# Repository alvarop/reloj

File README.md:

# Reloj - 7400 Series Digital Clock

This project was inspired by my dad's university digital systems project from the late 1970's. I found the writeup and schematic and decided to try and re-create it. You can see the results of the breadboard reproduction and explanations in [this twitter thread.](https://twitter.com/alvaroprieto/status/1239990814320680960)

After a while, I figured it would be fun to make a soldering kit out of it, which resulted in this.

The design is fairly close to the original, but with the addition of a crystal-backed alternate clock source. The 555 timer clock source works, but drifts like crazy, so if you want to use it as an actual clock, you still can with the alt source.

If you want to take a look at the actual paper, you can see the scanned version [here](files/sistemas_digitales.pdf).

## Design Files
You can get the latest files in the [github releases](https://github.com/alvarop/reloj/releases).

For v1.2, you can use my [OSHPark shared project](https://oshpark.com/shared_projects/LdUSEX5V) or by grabbing the gerbers from the release.

## Assembly Instructions
You can find semi-detailed assembly instructions [here](INSTRUCTIONS.md).

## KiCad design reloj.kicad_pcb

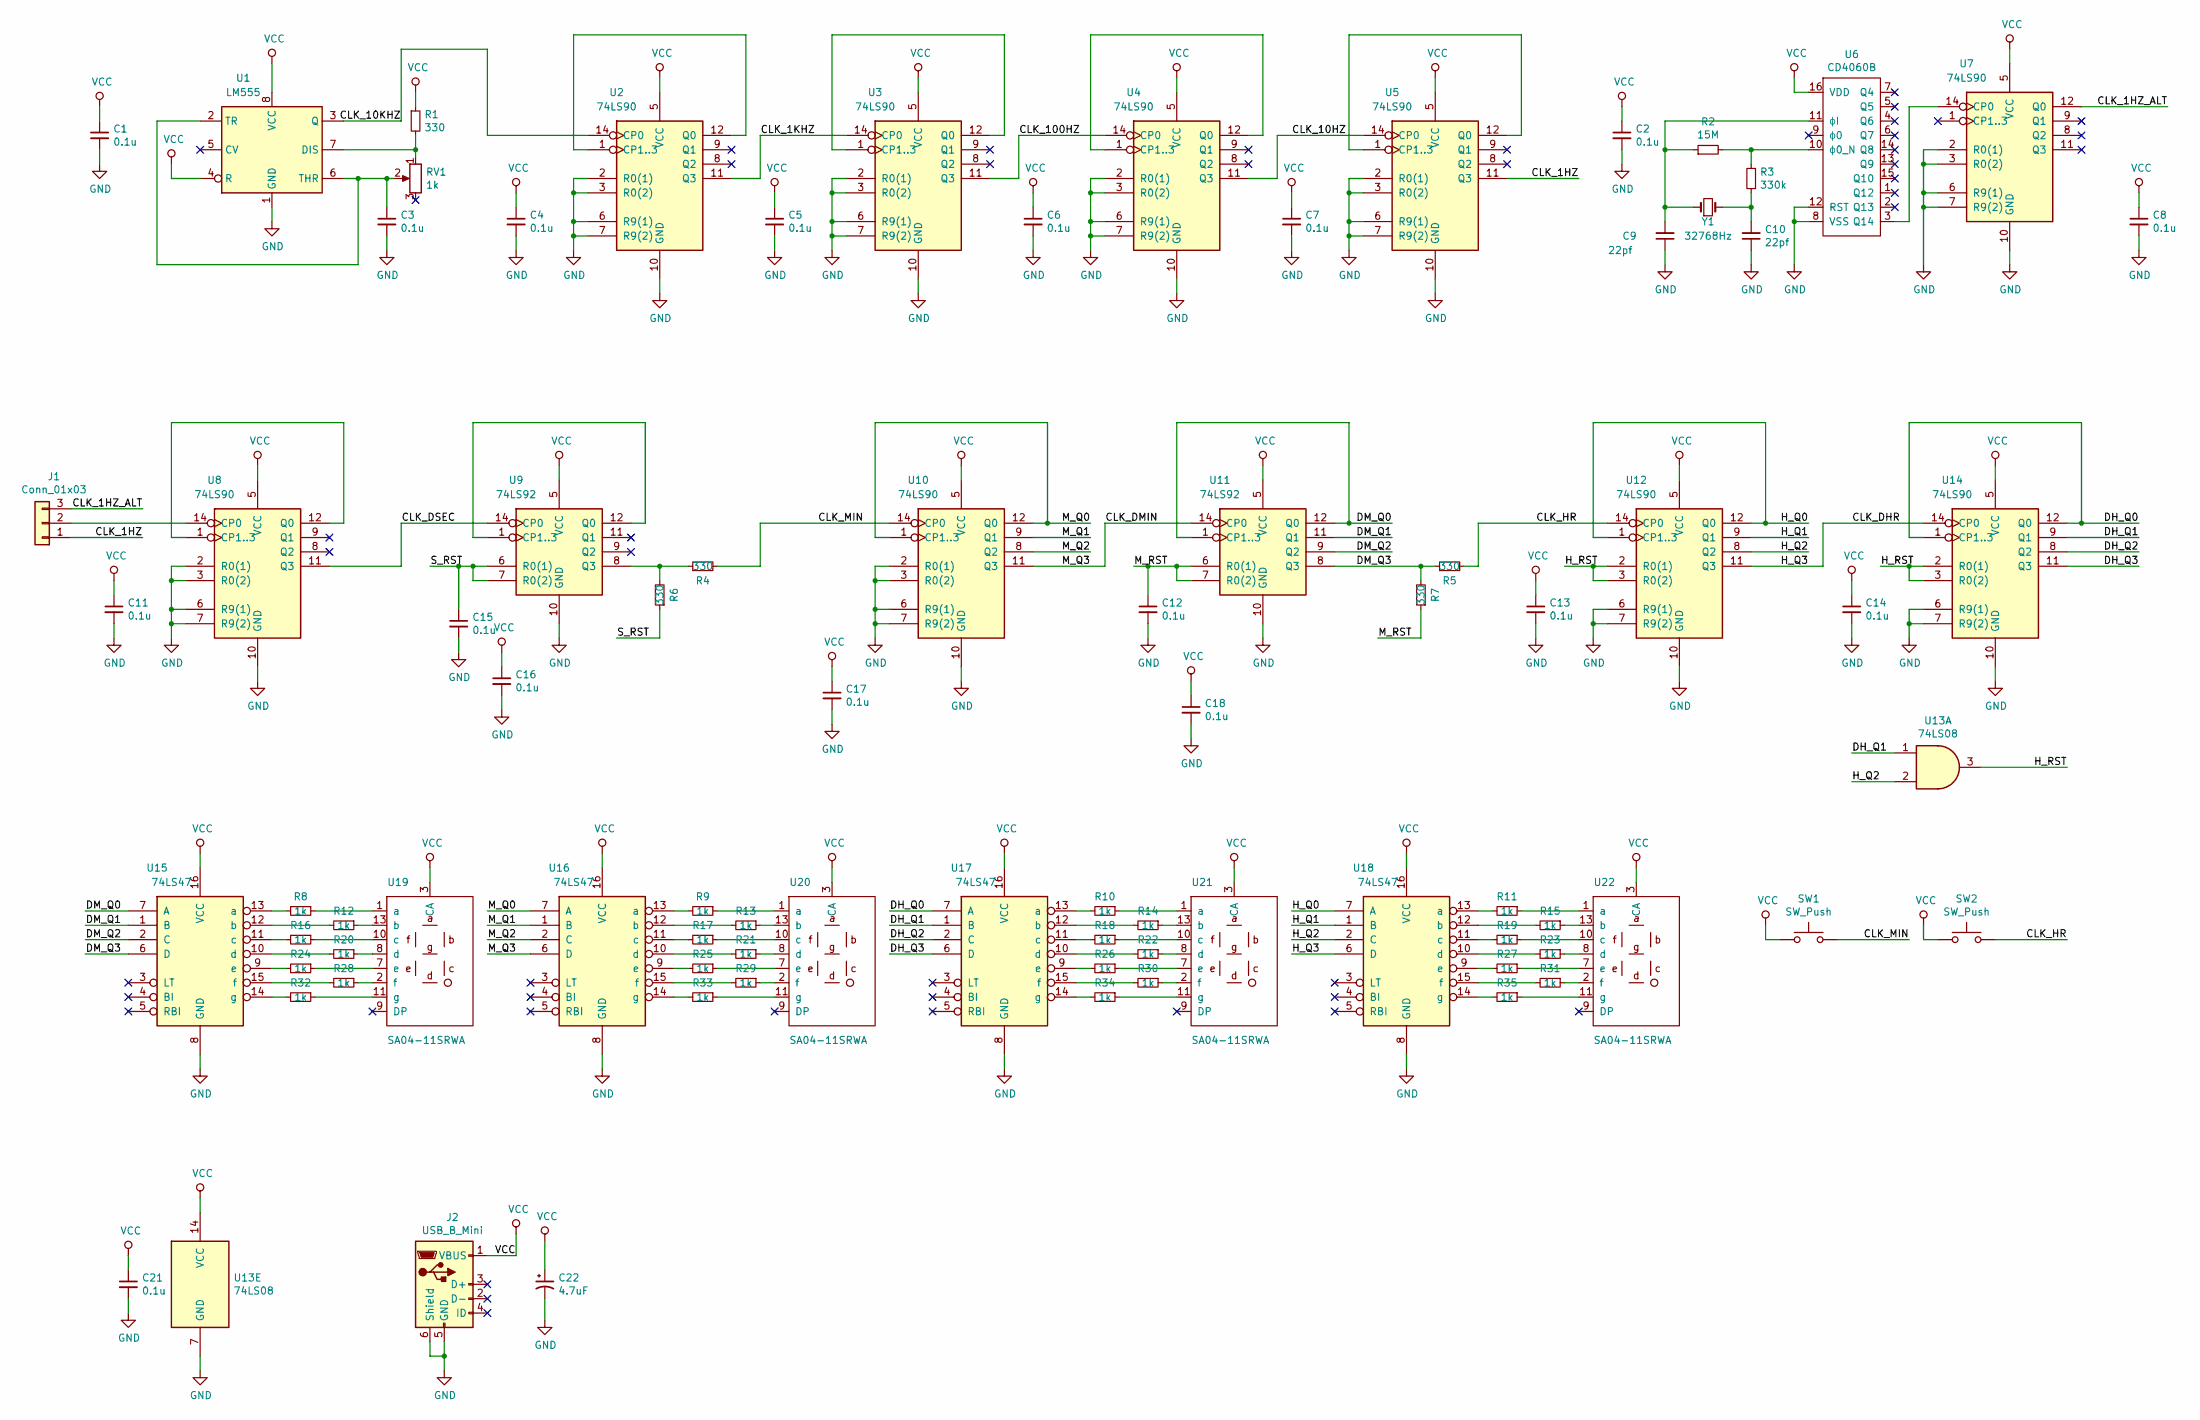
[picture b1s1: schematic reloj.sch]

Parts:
C1, C2, C3, C4, C5, C6, C7, C8, C11, C12, C13, C14, C15, C16, C17, C18, C21: 0.1u; C_Disc_D3.8mm_W2.6mm_P2.50mm; MPN K104K15X7RF53L2
C9, C10: 22pf; C_Disc_D3.8mm_W2.6mm_P2.50mm; MPN ‎K220J15C0GF5TL2‎
C22: 4.7uF; CP_Radial_D5.0mm_P2.00mm; MPN ECA-2AM4R7
J1: Conn_01x03; PinHeader_1x03_P2.54mm_Vertical
J2: USB_B_Mini; TE_2172034-1; MPN ‎2172034-1‎
R1, R4, R5, R6, R7: 330; R_Axial_DIN0204_L3.6mm_D1.6mm_P5.08mm_Horizontal; MPN ‎CF18JT330R‎
R2: 15M; R_Axial_DIN0207_L6.3mm_D2.5mm_P7.62mm_Horizontal; MPN ‎RNV14FAL15M0‎
R3: 330k; R_Axial_DIN0204_L3.6mm_D1.6mm_P5.08mm_Horizontal; MPN ‎CF18JT330K‎
R8, R9, R10, R11, R12, R13, R14, R15, R16, R17, R18, R19, R20, R21, R22, R23, R24, R25, R26, R27, R28, R29, R30, R31, R32, R33, R34, R35: 1k; R_Axial_DIN0204_L3.6mm_D1.6mm_P5.08mm_Horizontal; MPN ‎CF18JT1K00
RV1: 1k; 3296Y-1-102LF; MPN 3296Y-1-102LF
SW1, SW2: SW_Push; TE_1825910-6; MPN 1825910-6
U1: LM555; DIP-8_W7.62mm; MPN NE555P
U2, U3, U4, U5, U7, U8, U10, U12, U14: 74LS90; DIP-14_W7.62mm; MPN ‎SN74LS90N‎
U6: CD4060B; DIP-16_W7.62mm; MPN ‎CD4060BE‎
U9, U11: 74LS92; DIP-14_W7.62mm; MPN ‎SN74LS92N‎
U13: 74LS08; DIP-14_W7.62mm; MPN ‎SN74LS08N‎
U15, U16, U17, U18: 74LS47; DIP-16_W7.62mm; MPN ‎SN74LS47N‎
U19, U20, U21, U22: SA04-11SRWA; MPN SA04-11SRWA‎
Y1: 32768Hz; CFS-206x; MPN CFS-20632768DZFB‎

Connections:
/CLK_1HZ: J1.1, U5.11 (Q3)
/CLK_1HZ_ALT: J1.3, U7.12 (Q0)
/CLK_1KHZ: U2.11 (Q3), U3.14 (CP0)
/CLK_10HZ: U4.11 (Q3), U5.14 (CP0)
/CLK_10KHZ: U1.3 (Q), U2.14 (CP0)
/CLK_100HZ: U3.11 (Q3), U4.14 (CP0)
/CLK_DHR: U12.11 (Q3), U14.14 (CP0), U18.6 (D)
/CLK_DMIN: U10.11 (Q3), U11.14 (CP0), U16.6 (D)
/CLK_DSEC: U8.11 (Q3), U9.14 (CP0)
/CLK_HR: R5.2, SW2.2, U12.14 (CP0)
/CLK_MIN: R4.2, SW1.2, U10.14 (CP0)
/DH_Q0: U14.1 (CP1..3), U14.12 (Q0), U17.7 (A)
/DH_Q1: U13.1, U14.9 (Q1), U17.1 (B)
/DH_Q2: U14.8 (Q2), U17.2 (C)
/DH_Q3: U14.11 (Q3), U17.6 (D)
/DM_Q0: U11.1 (CP1..3), U11.12 (Q0), U15.7 (A)
/DM_Q1: U11.11 (Q1), U15.1 (B)
/DM_Q2: U11.9 (Q2), U15.2 (C)
/DM_Q3: R5.1, R7.2, U11.8 (Q3), U15.6 (D)
/H_Q0: U12.1 (CP1..3), U12.12 (Q0), U18.7 (A)
/H_Q1: U12.9 (Q1), U18.1 (B)
/H_Q2: U12.8 (Q2), U13.2, U18.2 (C)
/H_RST: U12.2 (R0(1)), U12.3 (R0(2)), U13.3, U14.2 (R0(1)), U14.3 (R0(2))
/M_Q0: U10.1 (CP1..3), U10.12 (Q0), U16.7 (A)
/M_Q1: U10.9 (Q1), U16.1 (B)
/M_Q2: U10.8 (Q2), U16.2 (C)
/M_RST: C12.1, R7.1, U11.6 (R0(1)), U11.7 (R0(2))
/S_RST: C15.1, R6.1, U9.6 (R0(1)), U9.7 (R0(2))
CA: C1.1, C2.1, C4.1, C5.1, C6.1, C7.1, C8.1, C11.1, C13.1, C14.1, C16.1, C17.1, C18.1, C21.1, C22.1, J2.1 (VBUS), R1.1, SW1.1, SW2.1, U1.4 (R), U1.8 (VCC), U2.5 (VCC), U3.5 (VCC), U4.5 (VCC), U5.5 (VCC), U6.16 (VDD), U7.5 (VCC), U8.5 (VCC), U9.5 (VCC), U10.5 (VCC), U11.5 (VCC), U12.5 (VCC), U13.14 (VCC), U14.5 (VCC), U15.16 (VCC), U16.16 (VCC), U17.16 (VCC), U18.16 (VCC), U19.3 (CA), U19.14 (CA), U20.3 (CA), U20.14 (CA), U21.3 (CA), U21.14 (CA), U22.3 (CA), U22.14 (CA)
GND: C1.2, C2.2, C3.2, C4.2, C5.2, C6.2, C7.2, C8.2, C9.1, C10.1, C11.2, C12.2, C13.2, C14.2, C15.2, C16.2, C17.2, C18.2, C21.2, C22.2, J2.5 (GND), J2.6 (Shield), U1.1 (GND), U2.2 (R0(1)), U2.3 (R0(2)), U2.6 (R9(1)), U2.7 (R9(2)), U2.10 (GND), U3.2 (R0(1)), U3.3 (R0(2)), U3.6 (R9(1)), U3.7 (R9(2)), U3.10 (GND), U4.2 (R0(1)), U4.3 (R0(2)), U4.6 (R9(1)), U4.7 (R9(2)), U4.10 (GND), U5.2 (R0(1)), U5.3 (R0(2)), U5.6 (R9(1)), U5.7 (R9(2)), U5.10 (GND), U6.8 (VSS), U6.12 (RST), U7.2 (R0(1)), U7.3 (R0(2)), U7.6 (R9(1)), U7.7 (R9(2)), U7.10 (GND), U8.2 (R0(1)), U8.3 (R0(2)), U8.6 (R9(1)), U8.7 (R9(2)), U8.10 (GND), U9.10 (GND), U10.2 (R0(1)), U10.3 (R0(2)), U10.6 (R9(1)), U10.7 (R9(2)), U10.10 (GND), U11.10 (GND), U12.6 (R9(1)), U12.7 (R9(2)), U12.10 (GND), U13.7 (GND), U14.6 (R9(1)), U14.7 (R9(2)), U14.10 (GND), U15.8 (GND), U16.8 (GND), U17.8 (GND), U18.8 (GND)
unnamed: C3.1, RV1.2, U1.2 (TR), U1.6 (THR)
unnamed: C9.2, R2.1, U6.11 (ϕI), Y1.1
unnamed: C10.2, R3.2, Y1.2
unnamed: J1.2, U8.14 (CP0)
unnamed: R1.2, RV1.1, U1.7 (DIS)
unnamed: R2.2, R3.1, U6.10 (ϕ0_N)
unnamed: R4.1, R6.2, U9.8 (Q3)
unnamed: R8.1, U19.1 (a)
unnamed: R8.2, U15.13 (a)
unnamed: R9.1, U20.1 (a)
unnamed: R9.2, U16.13 (a)
unnamed: R10.1, U21.1 (a)
unnamed: R10.2, U17.13 (a)
unnamed: R11.1, U22.1 (a)
unnamed: R11.2, U18.13 (a)
unnamed: R12.1, U19.13 (b)
unnamed: R12.2, U15.12 (b)
unnamed: R13.1, U20.13 (b)
unnamed: R13.2, U16.12 (b)
unnamed: R14.1, U21.13 (b)
unnamed: R14.2, U17.12 (b)
unnamed: R15.1, U22.13 (b)
unnamed: R15.2, U18.12 (b)
unnamed: R16.1, U19.10 (c)
unnamed: R16.2, U15.11 (c)
unnamed: R17.1, U20.10 (c)
unnamed: R17.2, U16.11 (c)
unnamed: R18.1, U21.10 (c)
unnamed: R18.2, U17.11 (c)
unnamed: R19.1, U22.10 (c)
unnamed: R19.2, U18.11 (c)
unnamed: R20.1, U19.8 (d)
unnamed: R20.2, U15.10 (d)
unnamed: R21.1, U20.8 (d)
unnamed: R21.2, U16.10 (d)
unnamed: R22.1, U21.8 (d)
unnamed: R22.2, U17.10 (d)
unnamed: R23.1, U22.8 (d)
unnamed: R23.2, U18.10 (d)
unnamed: R24.1, U19.7 (e)
unnamed: R24.2, U15.9 (e)
unnamed: R25.1, U20.7 (e)
unnamed: R25.2, U16.9 (e)
unnamed: R26.1, U21.7 (e)
unnamed: R26.2, U17.9 (e)
unnamed: R27.1, U22.7 (e)
unnamed: R27.2, U18.9 (e)
unnamed: R28.1, U19.2 (f)
unnamed: R28.2, U15.15 (f)
unnamed: R29.1, U20.2 (f)
unnamed: R29.2, U16.15 (f)
unnamed: R30.1, U21.2 (f)
unnamed: R30.2, U17.15 (f)
unnamed: R31.1, U22.2 (f)
unnamed: R31.2, U18.15 (f)
unnamed: R32.1, U19.11 (g)
unnamed: R32.2, U15.14 (g)
unnamed: R33.1, U20.11 (g)
unnamed: R33.2, U16.14 (g)
unnamed: R34.1, U21.11 (g)
unnamed: R34.2, U17.14 (g)
unnamed: R35.1, U22.11 (g)
unnamed: R35.2, U18.14 (g)
unnamed: U2.1 (CP1..3), U2.12 (Q0)
unnamed: U3.1 (CP1..3), U3.12 (Q0)
unnamed: U4.1 (CP1..3), U4.12 (Q0)
unnamed: U5.1 (CP1..3), U5.12 (Q0)
unnamed: U6.3 (Q14), U7.14 (CP0)
unnamed: U8.1 (CP1..3), U8.12 (Q0)
unnamed: U9.1 (CP1..3), U9.12 (Q0)

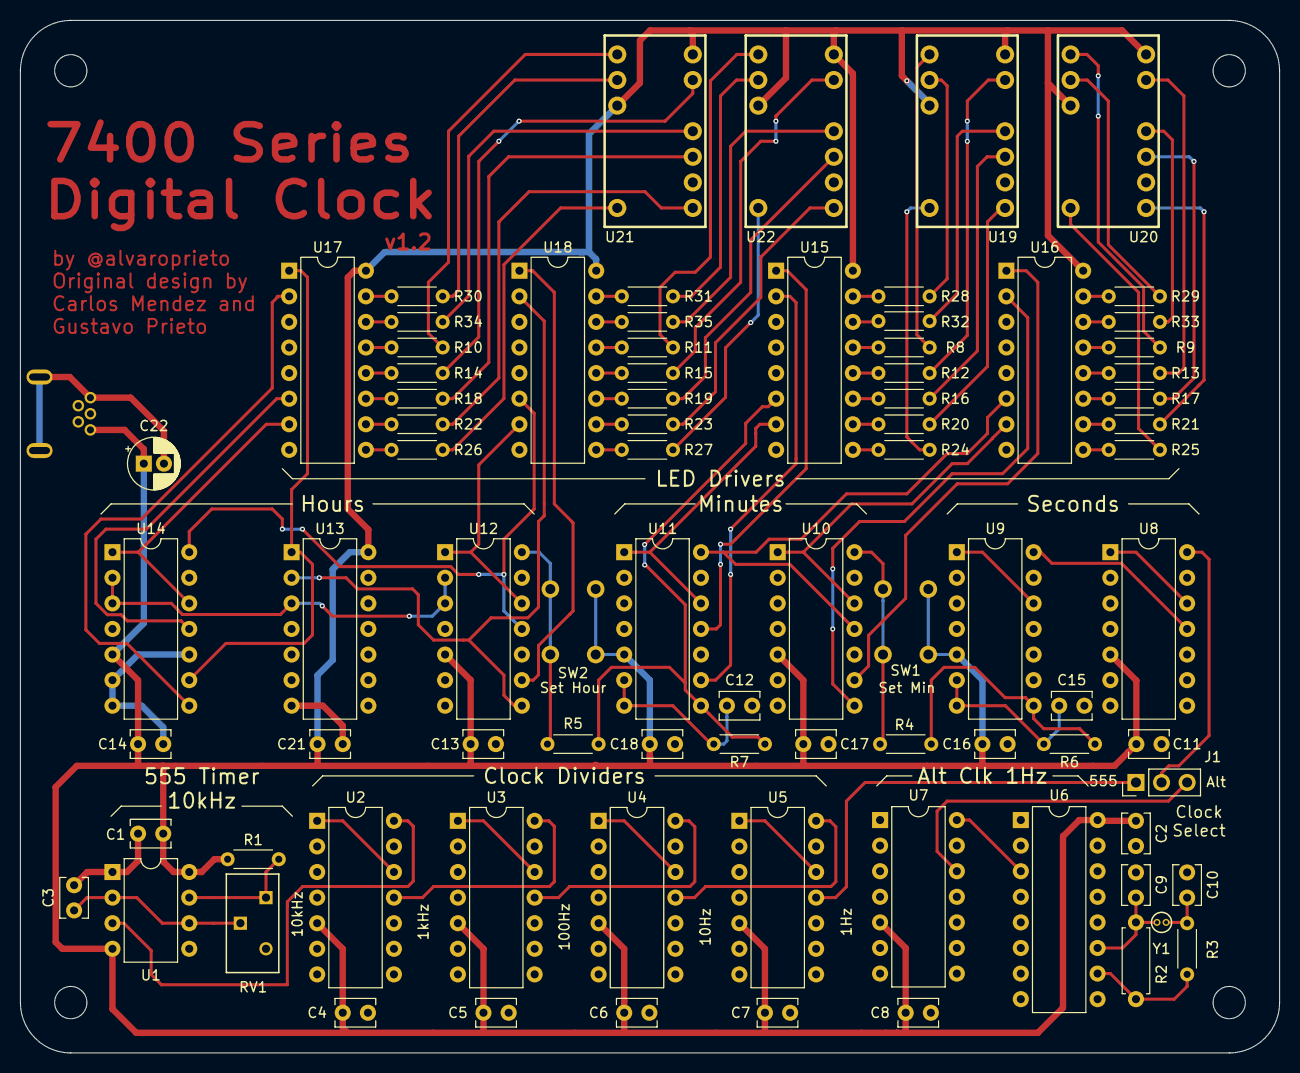
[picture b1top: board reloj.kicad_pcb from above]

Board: 2 copper layers, 125.0 x 102.5 mm, 83 parts (1 on the bottom side), 100 nets.

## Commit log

2020-03-23 First commit of reloj. Schematic mostly done
2020-03-24 Added most BOM items.
    Finished placement on pcb
2020-04-18 layout updates
2020-04-26 Added 4.7uF cap and cleaned up traces/silkscreen
2020-04-28 Finished layout and labels
    DRC passed and verified that remaining non-connected items are
    connected externally by components
2020-05-01 Added OSWH logo and changed title to be on copper layer
    Released to oshpark
2020-05-18 Fixed BOM
2020-05-30 Changes for v1.1
    Removed global reset button.
    Connected tens of minutes and tens of second counter resets to their Q3 output via RC filter. This prevents them from resetting themselves before clocking the next device.
    Reduced resistor for CLK_MIN and CLK_HR so that the buttons can still overpower it.
    Moved USB connector to other side and added silkscreen note
    Updated reference designators to make a bit more sense
    NOTE: New resistor values aren't final
2020-05-30 Forgot to commit changed netlists
2020-06-01 Minor updates to v1.1
    Updated 22pf cap BOM item
    Re-added mounting holes
    Polished a few traces
    Sent out to Bay Area Circuits
2020-06-06 Starting work on v1.2
    Connected U12's R0 to H_RST. Hours were going from 23->04 since the single digit hour wasn't resetting :/
    Removed both 0.1uF capacitors from CLK_MIN and CLK_HR... Not sure why they ended up there.
    I'm guessing I was thinking of debouncing but they are clock lines so the IC's were behaving poorly.
2020-06-07 Update layout with v1.2 fixes
2020-06-07 Change LED resistors to 1k to dim them a bit
    Change 555 timer R1 to 330ohm to reduce BOM complexity
2020-06-07 Switch to groun pour on botom layer
2020-07-01 Adding readme photos, and pdf scan
2020-07-01 Adding instructions and pictures
2020-07-01 Adding timelapse video
2020-07-29 Fixing link in readme
2020-11-23 Whoops. Thanks @elezaun!

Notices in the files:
parts and their libraries:
Copyright 2016 Accelerated Designs. All rights reserved.
